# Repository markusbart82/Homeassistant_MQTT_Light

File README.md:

# Homeassistant MQTT Light
Homeassistant compatible MQTT Light implementation for RGB+CCT LEDs. Uses ESP8266 and PCA9685.

The idea started because I wanted "white with a color tint" smart lights. But apparently, this is not supported by smart home tech yet. It's either RGB, or white, never a mix of these. So this lamp here identifies as RGB, but mixes white with it.

# How Color Mixing Works

This lamp can display both **colored light** and **tunable white** (from warm 2300K to cool 7000K), and uniquely, it can **mix white with color** — producing effects like "pink-tinted white" or "blue-tinted daylight" that most smart lights can't do.

## The Color Pipeline

Here's what happens internally when you send a color command:

1. **Input from Home Assistant**: You send RGB values (0-255) and a color temperature in mireds (142–435 mireds = 7000K–2300K)
2. **White extraction**: The algorithm finds the achromatic (gray/white) component by taking `min(R, G, B)` — this is the amount of white already present in the color
3. **Color separation**: The white component is subtracted from R, G, B, leaving only the pure chromatic (saturated) colors
4. **White distribution**: The extracted white is split between warm white (WW) and cold white (CW) LEDs based on the requested color temperature
5. **PWM output**: All 5 channels (R, G, B, WW, CW) are scaled to 12-bit resolution (0-4095) and sent to the PCA9685 PWM driver

## Examples

### Pure white with temperature
| Input | Output (R,G,B,WW,CW) |
|-------|----------------------|
| Warm white (2300K) | (0, 0, 0, 4095, 0) |
| Neutral white | (0, 0, 0, 2048, 2048) |
| Cool white (7000K) | (0, 0, 0, 0, 4095) |

### White with a color tint
| Input | What you see |
|-------|--------------|
| RGB(255,200,200) + 4000K | A soft pink-tinted white |
| RGB(200,220,255) + 5000K | A cool blue-tinted white |
| RGB(255,255,255) + 3500K | Pure warm white (no color tint) |

### Full color
| Input | What you see |
|-------|--------------|
| RGB(255,0,0) + any temp | Pure red (white channels off, `min(255,0,0)=0`) |
| RGB(128,64,32) + 3000K | Orange with warm white boost (`min(128,64,32)=32` → WW adds white) |

## Why This Matters

Traditional smart lights force you to choose: RGB *or* white. With this lamp, you get both simultaneously — perfect for ambient lighting where you want a colored accent light that still feels natural and bright.

# Invisible color temperature updates

Most smart lamps only let you update the color temperature while they are on. So they turn on with the previous color temperature and then dim to the right one. To combat this behavior, send a message with `brightness=1` and the desired color temperature to do an invisible update. The lamp will remain in its previous state (OFF, that is). Such low brightness values usually are not shown in most lamps, either.

# Homeassistant integration

The lamp supports autodiscovery and identifies as "ESP-dimmer-NUMBER", where the number is derived from the MAC address. Supported features:

- JSON schema
- ON/OFF
- Brightness
- Color temperature
- RGB
- Transitions
- Flashing

# Effects

The lamp supports the following effects:

- **Colorwheel** — slowly changes through the RGB spectrum
- **Undulation** — slowly undulates randomly near the previously selected color

# Stand-alone mode

As a fallback when Home Assistant is unavailable:

- On powerup, the lamp turns on with neutral white
- WiFi/MQTT reconnection is handled automatically in the main loop

# Hardware

The lamp uses the PCA9685 PWM driver IC (16 channels, 12 bits, up to 1.5kHz PWM, I2C at 400kHz) to interface with the LEDs. Currently, channels 0–4 are assigned R, G, B, WW, CW.

## Ledcontroller_3x

This PCB includes the ESP8266, PCA9685 and BLM3400 MOSFETs, for controlling 24V LED strips with a common +24V.

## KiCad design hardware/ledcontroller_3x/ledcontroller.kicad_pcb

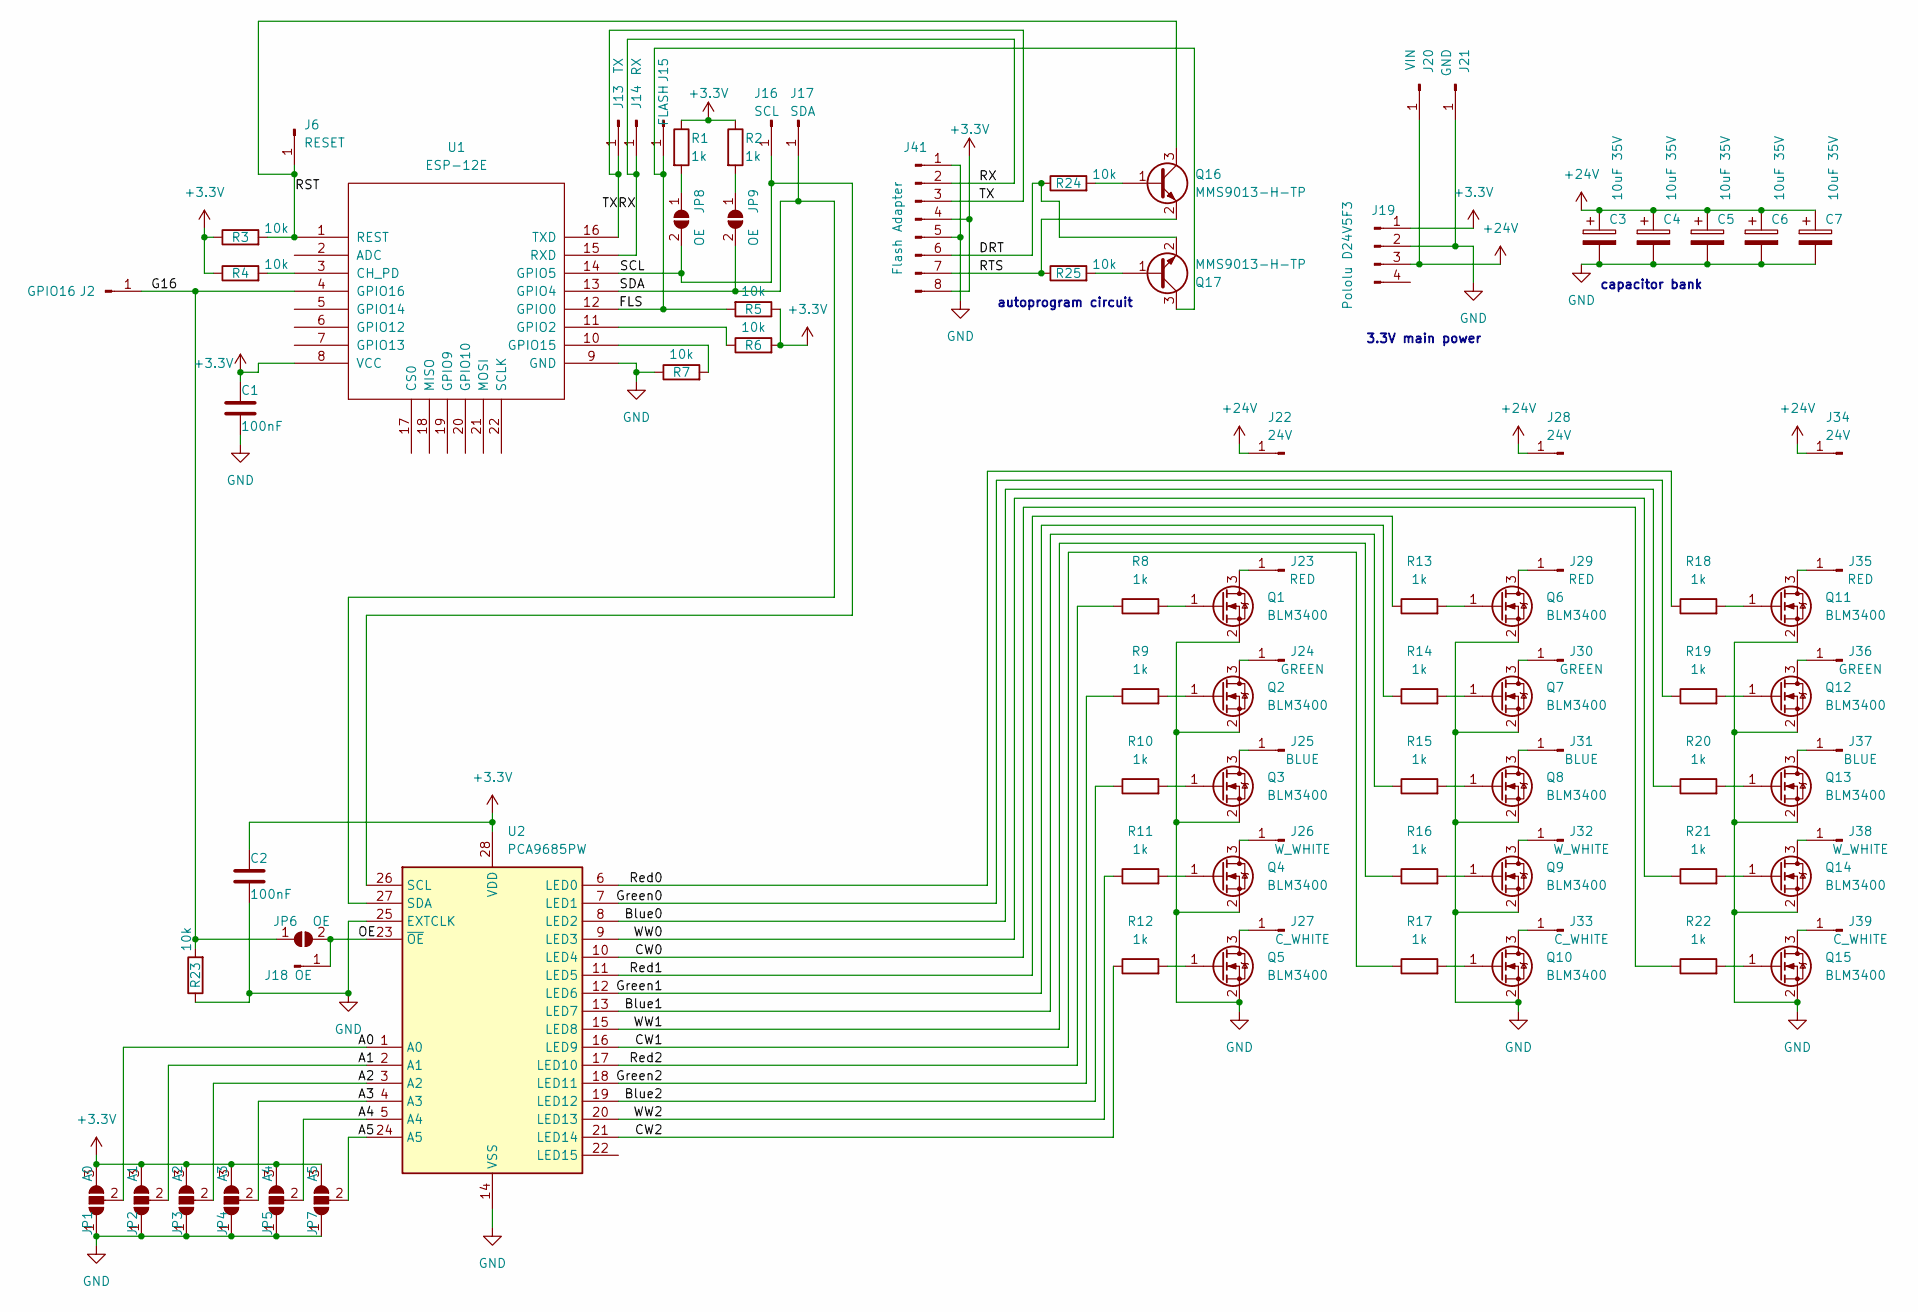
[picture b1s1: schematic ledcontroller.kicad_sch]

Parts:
C1, C2: 100nF; C_0805_2012Metric
C3, C4, C5, C6, C7: 10uF 35V; CP_Elec_5x5.4
J2: GPIO16; TestPoint_Pad_2.0x2.0mm
J6: RESET; TestPoint_Pad_2.0x2.0mm
J13: TX; TestPoint_Pad_2.0x2.0mm
J14: RX; TestPoint_Pad_2.0x2.0mm
J15: FLASH; TestPoint_Pad_2.0x2.0mm
J16: SCL; TestPoint_Pad_2.0x2.0mm
J17: SDA; TestPoint_Pad_2.0x2.0mm
J18: OE; TestPoint_Pad_2.0x2.0mm
J19: Pololu D24V5F3; PinHeader_1x04_P2.54mm_Vertical
J20: VIN; TestPoint_Pad_4.0x4.0mm
J21: GND; TestPoint_Pad_4.0x4.0mm
J22, J28, J34: 24V; TestPoint_Pad_3.0x3.0mm
J23, J29, J35: RED; TestPoint_Pad_3.0x3.0mm
J24, J30, J36: GREEN; TestPoint_Pad_3.0x3.0mm
J25, J31, J37: BLUE; TestPoint_Pad_3.0x3.0mm
J26, J32, J38: W_WHITE; TestPoint_Pad_3.0x3.0mm
J27, J33, J39: C_WHITE; TestPoint_Pad_3.0x3.0mm
J41: Flash Adapter; WingTAT_ED08BGFBK
JP1: A0; SolderJumper-3_P1.3mm_Open_Pad1.0x1.5mm
JP2: A1; SolderJumper-3_P1.3mm_Open_Pad1.0x1.5mm
JP3: A2; SolderJumper-3_P1.3mm_Open_Pad1.0x1.5mm
JP4: A3; SolderJumper-3_P1.3mm_Open_Pad1.0x1.5mm
JP5: A4; SolderJumper-3_P1.3mm_Open_Pad1.0x1.5mm
JP6, JP8, JP9: OE; SolderJumper-2_P1.3mm_Open_Pad1.0x1.5mm
JP7: A5; SolderJumper-3_P1.3mm_Open_Pad1.0x1.5mm
Q1, Q2, Q3, Q4, Q5, Q6, Q7, Q8, Q9, Q10, Q11, Q12, Q13, Q14, Q15: BLM3400; SOT-23
Q16, Q17: MMS9013-H-TP; SOT-23
R1, R2, R8, R9, R10, R11, R12, R13, R14, R15, R16, R17, R18, R19, R20, R21, R22: 1k; R_0805_2012Metric
R3, R4, R5, R6, R7, R23, R24, R25: 10k; R_0805_2012Metric
U1: ESP-12E; ESP-12E_SMD
U2: PCA9685PW; TSSOP-28_4.4x9.7mm_P0.65mm

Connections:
+3.3V: C1.1, C2.1, J19.1, J41.4, J41.8, JP1.3 (B), JP2.3 (B), JP3.3 (B), JP4.3 (B), JP5.3 (B), JP7.3 (B), R1.1, R2.1, R3.1, R4.1, R5.1, R6.2, U1.8 (VCC), U2.28 (VDD)
+24V: C3.1, C4.1, C5.1, C6.1, C7.1, J19.3, J20.1, J22.1, J28.1, J34.1
/A0: JP1.2 (C), U2.1 (A0)
/A1: JP2.2 (C), U2.2 (A1)
/A2: JP3.2 (C), U2.3 (A2)
/A3: JP4.2 (C), U2.4 (A3)
/A4: JP5.2 (C), U2.5 (A4)
/A5: JP7.2 (C), U2.24 (A5)
/ADC: U1.2 (ADC)
/Blue0: R20.1, U2.8 (LED2)
/Blue1: R15.1, U2.13 (LED7)
/Blue2: R10.1, U2.19 (LED12)
/CS0: U1.17 (CS0)
/CW0: R22.1, U2.10 (LED4)
/CW1: R17.1, U2.16 (LED9)
/CW2: R12.1, U2.21 (LED14)
/DRT: J41.6, Q17.2 (E), R24.1
/FLS: J15.1, Q17.3 (C), R5.2, U1.12 (GPIO0)
/G9: U1.19 (GPIO9)
/G10: U1.20 (GPIO10)
/G12: U1.6 (GPIO12)
/G13: U1.7 (GPIO13)
/G14: U1.5 (GPIO14)
/G16: J2.1, JP6.1 (A), R23.2, U1.4 (GPIO16)
/Green0: R19.1, U2.7 (LED1)
/Green1: R14.1, U2.12 (LED6)
/Green2: R9.1, U2.18 (LED11)
/MISO: U1.18 (MISO)
/MOSI: U1.21 (MOSI)
/OE: J18.1, JP6.2 (B), U2.23 (~OE)
/RST: J6.1, Q16.3 (C), R3.2, U1.1 (REST)
/RTS: J41.7, Q16.2 (E), R25.1
/RX: J14.1, J41.2, U1.15 (RXD)
/Red0: R18.1, U2.6 (LED0)
/Red1: R13.1, U2.11 (LED5)
/Red2: R8.1, U2.17 (LED10)
/SCL: J16.1, JP8.2 (B), U1.14 (GPIO5), U2.26 (SCL)
/SCLK: U1.22 (SCLK)
/SDA: J17.1, JP9.2 (B), U1.13 (GPIO4), U2.27 (SDA)
/TX: J13.1, J41.3, U1.16 (TXD)
/WW0: R21.1, U2.9 (LED3)
/WW1: R16.1, U2.15 (LED8)
/WW2: R11.1, U2.20 (LED13)
GND: C1.2, C2.2, C3.2, C4.2, C5.2, C6.2, C7.2, J19.2, J21.1, J41.1, J41.5, JP1.1 (A), JP2.1 (A), JP3.1 (A), JP4.1 (A), JP5.1 (A), JP7.1 (A), Q1.2 (S), Q2.2 (S), Q3.2 (S), Q4.2 (S), Q5.2 (S), Q6.2 (S), Q7.2 (S), Q8.2 (S), Q9.2 (S), Q10.2 (S), Q11.2 (S), Q12.2 (S), Q13.2 (S), Q14.2 (S), Q15.2 (S), R7.1, R23.1, U1.9 (GND), U2.14 (VSS), U2.25 (EXTCLK)
unnamed: J23.1, Q1.3 (D)
unnamed: J24.1, Q2.3 (D)
unnamed: J25.1, Q3.3 (D)
unnamed: J26.1, Q4.3 (D)
unnamed: J27.1, Q5.3 (D)
unnamed: J29.1, Q6.3 (D)
unnamed: J30.1, Q7.3 (D)
unnamed: J31.1, Q8.3 (D)
unnamed: J32.1, Q9.3 (D)
unnamed: J33.1, Q10.3 (D)
unnamed: J35.1, Q11.3 (D)
unnamed: J36.1, Q12.3 (D)
unnamed: J37.1, Q13.3 (D)
unnamed: J38.1, Q14.3 (D)
unnamed: J39.1, Q15.3 (D)
unnamed: JP8.1 (A), R1.2
unnamed: JP9.1 (A), R2.2
unnamed: Q1.1 (G), R8.2
unnamed: Q2.1 (G), R9.2
unnamed: Q3.1 (G), R10.2
unnamed: Q4.1 (G), R11.2
unnamed: Q5.1 (G), R12.2
unnamed: Q6.1 (G), R13.2
unnamed: Q7.1 (G), R14.2
unnamed: Q8.1 (G), R15.2
unnamed: Q9.1 (G), R16.2
unnamed: Q10.1 (G), R17.2
unnamed: Q11.1 (G), R18.2
unnamed: Q12.1 (G), R19.2
unnamed: Q13.1 (G), R20.2
unnamed: Q14.1 (G), R21.2
unnamed: Q15.1 (G), R22.2
unnamed: Q16.1 (B), R24.2
unnamed: Q17.1 (B), R25.2
unnamed: R4.2, U1.3 (CH_PD)
unnamed: R6.1, U1.11 (GPIO2)
unnamed: R7.2, U1.10 (GPIO15)

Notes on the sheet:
capacitor bank
autoprogram circuit
3.3V main power

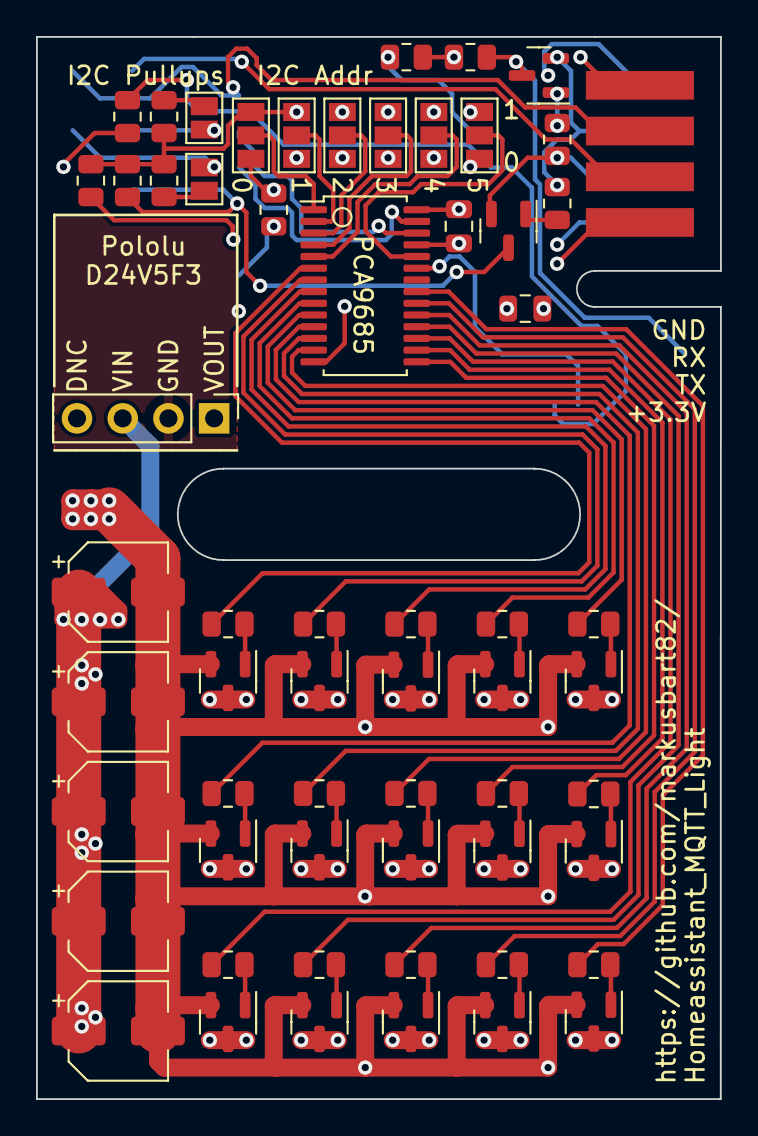
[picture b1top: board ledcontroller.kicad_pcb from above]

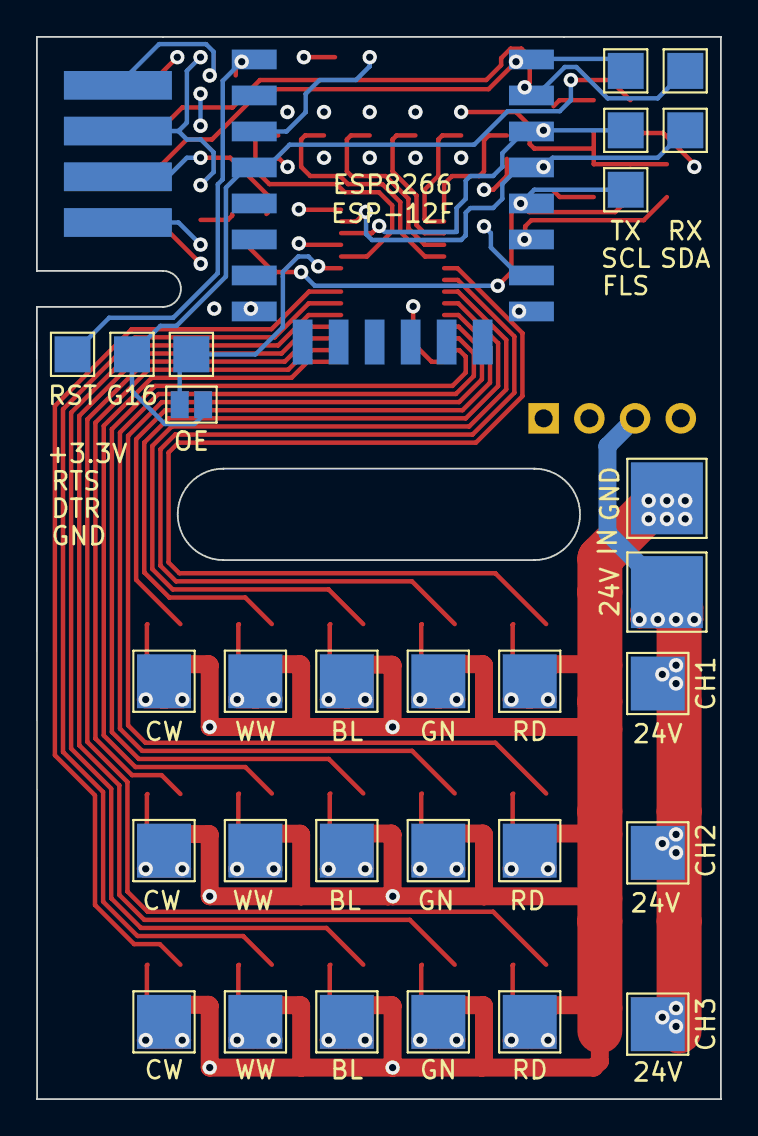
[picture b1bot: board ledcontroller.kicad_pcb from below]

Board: 4 copper layers, 38.0 x 59.0 mm, 90 parts (30 on the bottom side), 71 nets.

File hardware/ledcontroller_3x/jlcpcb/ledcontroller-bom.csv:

Designator,Footprint,Comment,LCSC Part Number
"C7,C6,C5,C4,C3",CP_Elec_5x5.4,10uF 35V,
"R14,R9,R18,R11,R10,R8,R22,R17,R13,R20,R19,R2,R15,R21,R1,R16,R12",R_0805_2012Metric,1k,
"R3,R7,R6,R23,R24,R25,R4,R5",R_0805_2012Metric,10k,
"Q3,Q10,Q4,Q5,Q1,Q11,Q12,Q6,Q7,Q14,Q15,Q13,Q8,Q2,Q9",SOT-23,BLM3400,
"Q16,Q17",SOT-23,MMS9013-H-TP,
"C2,C1",C_0805_2012Metric,100nF,
U2,TSSOP-28_4.4x9.7mm_P0.65mm,PCA9685PW,

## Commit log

2023-03-12 Initial upload
2023-03-12 added homeassistant and hardware chapters to readme
2023-03-12 added ledcontroller_3x
2023-03-12 added stand-alone mode and wifi switch
2023-04-10 Updated PCB to combat flickering with higher current LEDs or longer strips
2023-04-10 Removed sensor inputs - these should be a separate device. Also, improved the standalone mode time to light the default setting.
2023-04-10 All controls now reflected on all three output channels at the same time.
2023-04-10 Added effects "colorwheel" and "undulation".
2023-04-13 removed unnecessary define
2023-05-06 Updated PCB: additional decoupling capacitors, switchable I2C pullups, made OE pulled down instead of pulled up
2023-06-20 replaced ceramic capacitors with low ESR electrolytic caps
2023-06-20 added autoprogram circuit to schematic
2023-06-25 Added PCB Edge Connector for programming, rearranged lots of parts, removed pads of unused GPIOs
2023-06-26 PCB export for JLCPCB
2023-08-27 fixed typo in silkscreen
2024-06-23 PCB updates
2024-06-23 code re-write for maintainability (aka "I broke everything")
2024-07-06 started with PCA9685 controller integration
2024-07-20 removed old code imported from INO file
2024-07-20 updated FW upload settings
2024-07-20 Fixed warnings from ArduinoJson 6 to 7 upgrade
2024-07-20 added TODOs to fix later
2024-07-20 moved header files to appropriate path
2024-07-20 added default readme files for reference
2024-07-20 added stub of messagehandler callback function
2024-07-20 added more TODOs
2024-07-22 updated TODOs
2024-08-03 added update of physical controller values
2024-08-03 added auto-generated client name, fixed pubSubClient connection
2024-08-03 added initialization to messagehandler, updated comments
2024-08-03 added parser for incoming messages
2024-08-03 created new function in main for reception
2024-08-03 new APIs (getters) for buffered received message
2024-08-03 comments cleanup
2024-08-03 fixed compile error
2024-08-03 added channel number extraction from topic
2024-08-03 cleanup
2024-08-03 added initial status transmission after connection
2024-08-03 ArduinoJson migration StaticJsonDocument to JsonDocument
2024-08-18 added permanent colortemp, extracted effect type
2024-08-18 added channel data update, invisible colortemp update
2024-08-18 send state message back to HomeAssistant on received update
2024-08-18 removed old sins
2024-08-18 updated types for consistency
2024-08-18 fixed colortemp conversion functions' definitions
2025-04-12 updated hardware
2026-06-21 various fixes, debug output in many places
2026-06-21 made the project ready for AI-assisted development
2026-06-21 removed backup zip files, those aren't needed in git
2026-06-21 removed blocking reconnection loops
